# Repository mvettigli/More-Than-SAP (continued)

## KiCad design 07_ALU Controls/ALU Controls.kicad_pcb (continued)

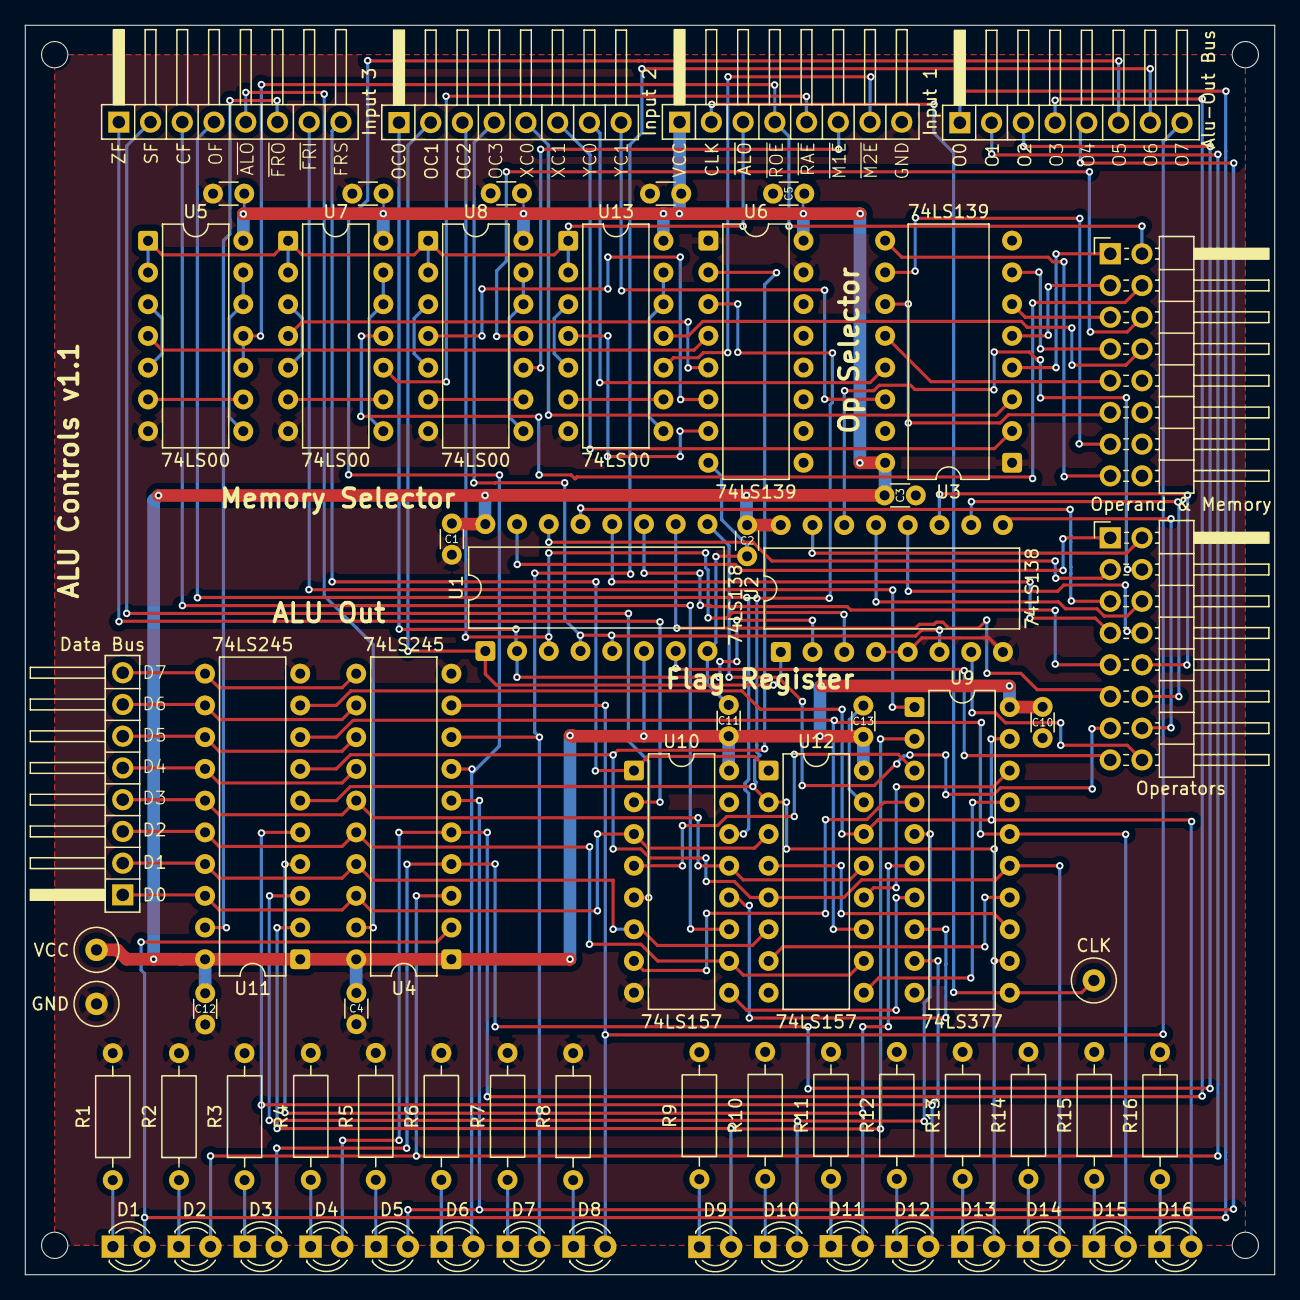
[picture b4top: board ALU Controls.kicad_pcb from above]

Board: 2 copper layers, 100.0 x 100.0 mm, 68 parts (0 on the bottom side), 115 nets.
